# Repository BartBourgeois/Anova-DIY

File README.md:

# Anova Precision Cooker Pro: reverse engineering & firmware recovery

> **Public export.** This repository is a periodic export of a private working repo. Issues and pull
> requests are welcome, but changes are made upstream and arrive with the next sync. The unit's serial
> number and the support ticket number are withheld; see "Legal and safety" below.
> Last sync: 2026-11-26.

Reverse-engineering notes, tools and recovery work for the **Anova Precision Cooker Pro (AN600)**.
The first goal was to **get a unit that died after an interrupted OTA firmware update cooking again**, by fixing
its original main board if that could reasonably be done, otherwise by building our own. **Done on 6 November 2026,
on the original board.** The rest goes on: the hardware mapped further, the schematics, diagnostics software.

**Any%.** My update stopped at 75 %; yours may have frozen on another number, so this project goes by Any%.
Speedrunners know the category: finish, by whatever route works. We got there: nine days from the stalled update to
the first cook.

## It cooks again (6 November 2026)

Dead on 29 October, the morning after an update stalled at 75 %. Cooking again on 6 November, on its original main
board: the buttons and the display, Wi-Fi and the app, and a 54 °C test cook held on point for ten minutes.

- **What was wrong:** the Wi-Fi chip had locked itself. Its security-alert counter stood at the limit, where the
  chip refuses to run until it is reprogrammed. The update's leftovers on the flash were harmless (the chip's own
  safeguard undoes them), the update never reached the Bluetooth chip, and the power board was fine all along.
  What raised the alerts is still open.
- **How it was fixed:** both chips' flash backed up first, each read twice with the same checksum. Then the Wi-Fi
  chip was reprogrammed through its own boot loader with the chip maker's tool: the current firmware, and the unit's
  own files carried over from the backup. Only the chip maker's documented procedures; no firmware is published here.
- **The story:** [Day six: it cooks again](blog/posts/2026-11-06-it-cooks-again.md). The record:
  [timeline](docs/timeline.md). The procedures: the [flash backup handbook](docs/flashbackup/index.md) and the
  [recovery handbook](docs/recovery/index.md).

> Not affiliated with or endorsed by Anova Applied Electronics, Inc. (Anova Culinary). Everything here is at your own risk.
> The power board carries **mains voltage**. Never open or probe a unit that is plugged in.

## Why

*Written on 2 to 4 November, while the cooker was dead, and left as it was written. Its questions are answered in
[It cooks again](#it-cooks-again-6-november-2026).*

I paid what a premium product from a premium brand costs, about $450, and expected exactly that. The cooker died
right after a firmware update was interrupted. Not dropped, not flooded, not abused: the update stalled at 75 %, and
after a power cycle the unit was dead. No beep, no display, nothing. I have no doubt the update killed it: it was the only event, the timing matches, nothing else happened.
By this repo's own standard that stays "likely" until a measurement rules out a coincidental power-supply failure.
The first one, on 4 November, points that way: the power board still puts 5.01 V on the connector with the main board
unplugged. Whether it holds up under load is the next check.

In my view that should not be possible in 2026. A $10 smart plug routinely survives a botched update: it keeps the
old firmware until the new one has proven itself. The Wi-Fi chip in this cooker even has that mechanism built in
(TI documents an OTA rollback for it). Yet here we are.

I'll own my part. The cooker worked perfectly, and I updated it anyway. I work in IT, where update discipline is
drilled into you, and I also know the older rule: if it isn't broken, don't fix it. So yes, I pressed the button.
But in my book, a vendor that offers updates is responsible for what an interrupted one does. The hardware that
lets a device survive a botched update is a second copy of the firmware in flash, a dollar's worth of memory at
most. This cooker has 8 MiB of flash, and its chip's maker documents a rollback mechanism for exactly this case
([recovery-strategy.md](docs/firmware/recovery-strategy.md)). It didn't save my cooker. Finding out why is part of
this project.

And that is the most interesting question in this whole story. The mechanism exists on this very board, so there are
only three ways to end up here: the firmware doesn't use it; or the update touched something it doesn't cover (the
BLE chip, the file system itself); or the failure isn't in the Wi-Fi chip at all. The flash dump will tell. Whichever
answer it is, it goes here, with the evidence.

Anova's answers so far (ticket opened 2026-10-29): leave it plugged in overnight; then that the unit is out of
warranty; then 10 % off a new one. For perspective: 10 % is the usual newsletter sign-up discount on Anova's own
site, and the Pro itself has sold at about half price in seasonal promotions (Amazon US, Black Friday 2020;
[sources](docs/references.md#anova)). On 2026-11-01 I asked for one of four things: a firmware image with recovery
instructions, a replacement main board at my cost, a mail-in reflash, or a refurbished unit. None of the four came:
the reply (2026-11-02) was a reset procedure on the touch panel, which had been dark since the update. On 2026-11-06,
with the cooker cooking again, I told them how it was fixed and offered the details to their firmware team; on
2026-11-08 they forwarded my account to their engineering and development teams. The whole exchange is on record, word for word: [correspondence](docs/correspondence.md). To me, a discount on
a replacement isn't support, it's a sales offer.

It's sad, and I feel tricked: a premium price should buy an update process that can't kill the device. I'd rather
spend thousands of euros on debugging hardware, beta boards and DIY electronics than buy a new Anova. Spent on
tools so far: about €545, two days in ([list](docs/hardware/bench-setup.md#spent-so-far-2026-11-02)).

So I'll keep at this until this dead Pro cooks again, whatever it takes. If Anova helps: good, cheaper for me, and I'll
say so here. If not, make no mistake, the cooker will cook. Everything I learn on the way is in this repo, so the next
person with a dead one doesn't start from zero.

This repository stays online, whatever the outcome. I will not delete it. It documents the progress and the process as
they happen: every change upstream is published within seconds. The public repository is a snapshot by design, the
current state and nothing else; the dated record is the [timeline](docs/timeline.md), and when a statement of
substance about the cooker turns out wrong, the correction goes there with its date. It is what it is.

raptox

## What this project wants

1. **This cooker cooking again.** **Done, 6 November 2026**, on its original main board
   ([how](#it-cooks-again-6-november-2026)). Nothing waited on anyone.
2. **A documented recovery path for every Precision Cooker Pro that fails the same way.** Everything learned here is
   public under an open licence ([LICENSE.md](LICENSE.md)), so the next owner starts from this page, not from zero.
3. **From Anova, any of the four things asked on 2026-11-01:** a firmware image with recovery instructions, a
   replacement main board at my cost, a mail-in reflash, or a refurbished unit. Or, better for every owner: an
   official, documented recovery procedure for units out of warranty. Help gets credited here, in full.

How the work is done: read-only first, a verified backup before any write, every claim with a confidence label and
a source, every step in the [timeline](docs/timeline.md). This project documents a repair. It distributes no firmware
and publishes no way around any protection (see [Legal and safety](#legal-and-safety)).

## The patient

| | |
|---|---|
| Model | Anova Precision Cooker Pro, type **AN600-20** (EU, 220-240 V) |
| FCC ID | [`2APBOAN600`](https://fccid.io/2APBOAN600) (granted 2018-09-16, tested as AN600-10 / 120 V) |
| Symptom | OTA update via the Anova app stalled at 75%. After a power cycle the unit is completely dead: no beep, no display, no LEDs, and nothing on Bluetooth or Wi-Fi. |
| Status | **Cooking again since 2026-11-06**: the Wi-Fi chip had locked itself; reprogrammed ([how](#it-cooks-again-6-november-2026)). |
| Reference | A second, **working** Precision Cooker Pro is available for read-only comparison. |

Full story: [docs/incident.md](docs/incident.md). Everything since then, dated: [docs/timeline.md](docs/timeline.md).
The narrative, in instalments: [blog](blog/index.md).

**Website:** <https://cooked.raptox.be/>, rebuilt from this repo on every push.

## What's inside

From raptox's unit (main board, 2026-11-01) and the FCC photos (everything else).

| Board | Key parts |
|---|---|
| **Main board** `ANOVA_PRO_MAIN_V2.0` | **U1 TI CC3220S** Wi-Fi MCU, boots from **U15/U16 XMC XM25QH64A** (8 MiB SPI NOR, SOP-8 208 mil) · **U7 TI CC2640R2F** BLE MCU (internal flash) · unidentified U14 `T3018` (QFN-40), U13 `4637` (QFN-20, next to the speaker) · debug: J29 (1x3, empty: the serial link between the two chips, both directions, and the Wi-Fi chip's boot-loader port), J14 (4-way DIP footprint, empty, the Wi-Fi chip's three boot straps), Tag-Connect J37/J38, TP groups · 30-pin FPC J8 to the power board · J9 speaker · 6 touch keys, about 135 discrete LEDs forming 3 x 4 seven-segment digits |
| **Power board** `ANOVA_PRO_POWER_REV01` | AC/DC flyback daughterboard (F1 T2A/250V) · heater relay · main fuse · DC/DC buck (6.8 uH) · several unidentified ICs · 30-pin FPC J8 · wire terminals for heater/pump/sensors · PCB "finger" that probably carries the water-temperature sensor |

Details: [docs/hardware/overview.md](docs/hardware/overview.md) ·
[main board](docs/hardware/main-board.md) · [power board](docs/hardware/power-board.md) ·
[component list](docs/hardware/components.md) · [opening the head](docs/hardware/disassembly.md) ·
[bench setup & debugging](docs/hardware/bench-setup.md) · [photo log](docs/photos.md)

## Annotated photos

**raptox's unit**, main board component side, stitched from 335 microscope frames (2026-11-03):

At 100 % (229 px/mm): the zoomable [mosaic viewer](docs/mosaics.md) or the
[lossless PNG](https://github.com/BartBourgeois/Anova-DIY/releases/download/mosaics/2026-11-03_main_component-side_mosaic.png).

The first phone photo of the same side (2026-11-01): [annotated](images/annotated/main_component-side_own.png).

**All photos in this project are our own unless marked otherwise.** The images below marked "FCC" come from the
public FCC filing for this product (FCC ID 2APBOAN600, internal-photos exhibit 3999178, 2018 sample) and carry that
source in their legend.

FCC sample (2018), source: FCC ID 2APBOAN600, exhibit 3999178:

| | |
|---|---|
|  |  |
| Main board, component side | Main board, LED / touch side |
|  |  |
| Power board, top | Power board, bottom |
|  |  |
| Head opened (assembly) | Front bezel (from the back) |

Box colour = category, outline = confidence (solid confirmed, dashed likely, dotted guess).
Click an image for its callout table.

## Roadmap

Two cases, both planned, in [docs/roadmap.md](docs/roadmap.md): Anova helps (unlikely; documented in full if it
happens, and the repair part ends there), or we do it ourselves, all the way, with every step the tools allow. Either
way the project doesn't stop at the point of no return, which has passed.

The headline steps of the do-it-ourselves case: **4K microscope imaging of every board**, tile by tile, into
measurable mosaics; transillumination for the inner copper layers; **reverse-engineering the schematics**, net by net,
since Anova's are confidential in the FCC filing; logic analyser and UART on the boot sequence; a verified dump of the
flash; rehearsals of every write on a known-good chip; and, if the board can't be fixed, a board of our own. The
phase view below is the short version.

| Phase | Goal | Status |
|---|---|---|
| 0 | Document hardware from the public FCC filing | **done (first pass)** |
| 1 | Open the dead unit: own high-res photos, read chip markings, measure supply rails; compare (read-only) with the working unit | **in progress**: opened, main board photographed, markings read; main board's component side stitched from microscope frames at about 229 px/mm ([photo log](docs/photos.md#2026-11-03-microscope-mosaic-main-board-component-side)); next: the other sides and backlight; the power board's 5 V measured (4 Nov), the rails under power todo |
| 2 | Find and map debug interfaces: J29, J37/J38 (Tag-Connect), DIP J14, test points; CC3220 SOP straps, UART, JTAG/SWD; CC2640R2F cJTAG. Identify power-board U2 (MCU?) and map the J8 pinout unpowered. Draw the schematics from the images and the continuity map. | **in progress**: J8's supply and ground (4 Nov); the flash bus, the three boot straps with their pull-downs, the serial header J29 and nine bare pads measured to the chips (5 Nov, [test points](docs/hardware/testpoints.md)); J37 and J8's signal lines next |
| 3 | **Back up first**: full read-only dump of the CC3220 serial flash (and of the CC2640R2F flash if readable), read twice and hash-verified | **done**, 6 Nov: the serial flash by clip with the Wi-Fi chip held in reset, the CC2640R2F over its cJTAG port; each read twice, identical, copied off the machine ([flash backup handbook](docs/flashbackup/index.md)) |
| 4 | Analyse the dumps: SimpleLink filesystem layout, OTA state, which chip the failed update targeted | **done**, 6 Nov: the file system intact, the interrupted update in a state the chip rolls back; the CC2640R2F untouched by it; the CC3220 **locked** (its security-alert counter at the limit) ([timeline](docs/timeline.md)) |
| 5 | Recovery, depending on Phase 4. The broken file alone, replaced through the UARTLOAD boot loader, keeps the unit's network address and cloud identity, but a production-mode boot loader refuses file writes (rehearsed 6 Nov); then a full image with the unit's own readable files carried over from the backup, or RET_FACTORY_IMAGE (both erase the protected ones); a CC2640R2F reflash if that chip is the victim | **done**, 6 Nov: a full image through the UARTLOAD boot loader, the current firmware with the unit's own files from the backup; the lock cleared, **the cooker cooks** ([the story](blog/posts/2026-11-06-it-cooks-again.md)) |
| 6 | Diagnostics software (UART console, flash-dump parser, BLE/Wi-Fi local API client, ...) | later |
| B | If the board can't reasonably be fixed: our own main board (ESP32-S3, headless first), or our own firmware on the original CC3220 | **committed fallback** ([plan B](docs/plan-b-custom-mainboard.md)) |

The recovery reasoning lives in [docs/firmware/recovery-strategy.md](docs/firmware/recovery-strategy.md).

Phases 1-2 are run as an **open exploration**: no gates, every tool used to learn as much as it can, route chosen
only when the findings make it obvious.

## Legal and safety

- **Not affiliated.** Anova and Precision Cooker are trademarks of Anova Applied Electronics, Inc., used here only
  to identify the product. This project is not affiliated with, endorsed by or sponsored by Anova.
- **Own device, for repair.** Everything here comes from examining a device raptox owns, from public FCC filings and
  from public chip-maker documentation (TI). The aim is to repair it. The procedures described are the ones TI
  documents for its own chips; in the author's reading (not legal advice), nothing here circumvents a technical
  protection.
- **Never distributed:** Anova firmware, flash dumps or fragments of them; keys, certificates or credentials; anything
  that gives access to Anova's servers; Anova's user manual; the FCC exhibit PDFs themselves (public at
  [fccid.io/2APBOAN600](https://fccid.io/2APBOAN600), SHA-256 in [docs/references.md](docs/references.md)).
- **Statements about Anova** are dated facts from the support correspondence, quoted word for word on the
  [correspondence page](docs/correspondence.md) or paraphrased, or opinions labelled as such. Anova staff are never named.
- **Safety, no warranty.** The power board carries mains voltage, which can kill. Opening the unit voids its warranty
  and its CE/FCC certification, radio included; a modified unit is not a certified appliance. Never leave a modified
  heater unattended. Everything here is at your own risk, without warranty or liability of any kind
  ([LICENSE.md](LICENSE.md), at the root of the public repo).
- The author is an engineer, not a lawyer. This is engineering documentation, not legal advice.
- The full statement of the bounds this project works within, for the United States, for Belgium and the EU, and for
  everywhere else: [docs/legal.md](docs/legal.md).

## Sources

Hardware information comes from raptox's own unit and the public FCC filing for `2APBOAN600` (the schematics and block
diagram are confidential and not available). See [docs/references.md](docs/references.md).

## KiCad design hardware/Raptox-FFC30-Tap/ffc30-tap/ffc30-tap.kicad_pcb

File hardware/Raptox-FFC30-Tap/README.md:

# FFC30 tap

A gated pass-through board for any 30-way flat flex cable (FFC) at 0.5 mm pitch. It sits between two boards, brings
every line out on a 2.54 mm **bus** pin with a ground pin beside it (for a logic analyser such as the DSLogic Plus),
and puts a **jumper gate** on each side: a cap per line decides whether that line of side A, of side B, or of both
reaches the bus. Every cap on = a plain pass-through. Nothing on the board is specific to one device; it was first
made for the Anova Precision Cooker Pro's J8 link ([pinout](../../docs/hardware/j8.md)).

**Status (2026-11-18): rev D drawn, not ordered** (in [ffc30-tap/](ffc30-tap/), DRC clean). **Rev C is in production
at JLCPCB** (ordered 2026-11-12, 5 boards, fully assembled), frozen with its own instructions in [revC/](revC/README.md).

## Rev D
- 96 x 92 mm, 4 layers, 1.6 mm, black solder mask.
- Two sockets, the same part on both sides: HanElectricity **05A20L30P** (LCSC C5362159), bottom contact, flip lock,
  2.0 mm high, for 0.3 mm FFC. Contacts on one face only, so neither cable can go in upside down. Land pattern from
  HanElectricity's drawing 05A20LXX (rev A, 2015-05-03): signal pads 0.30 x 1.25 mm, mounting pads 2.00 x 3.00 mm.
  The body's front (cable entry) is flush with the board edge (`likely`, within about 0.2 mm). Unchanged from rev C.
- **One row per line, 30 rows** (pin 30 at the top, pin 1 at the bottom, in the order of the socket pads), six pins
  a row in three pairs, one empty pitch between the pairs so a cap can't bridge two of them:

  ```
  socket A ─ [ A   BUS ]   [ BUS  GND ]   [ BUS   B ] ─ socket B
               gate A          bus           gate B
  ```
  - **A n** = the left socket's pin n, **B n** = the right socket's pin n, **BUS n** = the three BUS pins of row n
    (one net).
  - Cap on **A|BUS**: side A's line n on the bus. Cap on **BUS|B**: side B's line n on the bus. Both: line n passes
    through, as in rev C. Neither: the two sides are apart on that line, and each can be probed or driven on its own.
  - Cap on **BUS|GND**: line n joined to the ground rail, as in rev C. The rail (the GND column and the two inner
    ground planes) floats until one is on.
- Six 2x15 headers (LCSC C56496, 2.54 mm, straight), two per pair, butted end to end at the middle (pins 15 and 16).
- Every line on the top layer: a 45 degree fan-out from each socket straight into its outer column; the BUS link from
  the bus pair to gate B runs round the ground pin in the gap below its row. In1 and In2 are solid ground planes.
- Silkscreen: the row numbers (in both gaps), the column and pair names, SIDE A / SIDE B, the ground box, the title
  and cooked.raptox.be.

## Using it
1. **Cables:** both of the same type (contacts on the same side at both ends, "type A"), contacts down into the
   sockets.
2. **The board whose pin numbers you want goes in the LEFT socket (side A).** Row n is then its pin n, if its
   connector has bottom contacts and numbers its pins like these sockets (pin 1 on the left, seen from where the
   cable enters). Otherwise row n is its pin 31 - n. The lines pass through correctly either way.
3. **Before power,** with the caps on and only one board's cable in, ring the pins you know (its supply pins
   together, its ground pins together) to make sure of the numbering.
4. **Gates, in this order:** ground lines first (A|BUS and BUS|B on every ground row), then the supply, then the
   signals; take them off in the reverse order. A side with its supply connected and its ground open finds a ground
   through the signal lines and the chips' protection diodes.
5. **Ground rail:** a cap on BUS|GND only on a row that *is* ground. A cap there on a supply row shorts the supply.
   One or two are enough for slow signals (DreamSourceLab's DSView guide: one common ground below about 5 MHz).
6. **Probes:** the signal lead on a BUS pin (or on an A or B pin to see one side before its gate), its ground lead on
   the GND pin of the row.
7. **Mains:** a PC-grounded analyser connects the PC's earth to the board's ground. With a mains-powered board in the
   chain, check that its ground is isolated from mains first.
8. **Underneath:** the header pins stick out about 1.4 mm under the board (3 mm tails through 1.6 mm), plus solder.
   Stand the board on four M2 nylon standoffs, at least 6 mm, in the corner holes, or on a non-conductive surface.
   Never on metal: it joins pins, and a supply line on ground shorts the supply.

## Ordering at JLCPCB
Three files, all in `ffc30-tap/fab/`:

| Step | File | Settings |
|---|---|---|
| PCB | `ffc30-tap_gerbers_JLC.zip` | 4 layers, 96 x 92 mm (read from the files), 1.6 mm, **black** solder mask, the default 4-layer stackup |
| Assembly | | **Standard** PCBA (the headers are wave soldered, which Economic doesn't do), top side, edge rails as JLCPCB asks (rev C had them on the sides without sockets), **Confirm Parts Placement: Yes** |
| BOM | `jlc_bom.csv` | J1, J2 = C5362159 (socket); J3-J8 = C56496 (2x15 header). Both are extended parts; check stock |
| Placement | `jlc_cpl.csv` | Check every part in the placement preview, then confirm |

The CPL already carries two corrections for JLCPCB's own part models (measured in their placement viewer on
2026-11-12, set in `build_fab.py`; the copper itself follows the makers' drawings):
- **Sockets J1, J2:** JLCPCB's model of C5362159 sat 2.0 mm toward the board edge from the pads, so the CPL moves each
  socket 2.0 mm toward its pads. With that, the model's pins end about 0.15 mm inside the pads' tips and its body
  starts about 0.8 mm from them, as the footprint assumes.
- **Headers J3-J8:** JLCPCB's model of C56496 lies across the board at 0 degrees; the CPL turns them 90 degrees.

Still check in the placement preview, against [the render](ffc30-tap/render_top.png): the sockets' cable openings
face the board edges and their pins sit on the 30 pads; the headers stand over their two columns, two butted end to end per pair.

Rev C's first quote (2026-11-12, 5 boards, before shipping): PCB EUR 14.40 (black mask EUR 7.20 of it), Standard PCBA
EUR 43.39, total EUR 57.79; PCB 3 days, assembly 5-6 days.

## Regenerating
The board is generated from code: change `generate_board.py`, never the `.kicad_pcb` by hand. With KiCad 10's own
Python, in `ffc30-tap/`:

```sh
"<KiCad 10>/bin/python.exe" -I generate_board.py   # board, footprint library, fp-lib-table
"<KiCad 10>/bin/python.exe" -I build_fab.py        # DRC (must be clean), gerbers, drill, BOM, CPL, renders
```

## Revisions
- **rev A** (2026-11-12, [revA/](revA/), not ordered): 2 layers, one 2x15 header, sockets with contacts on both faces
  (X05A20H30G). One cable inserted upside down mirrors the bus (pin n to 31 - n): on the cooker that feeds the main
  board backwards. Its header numbers read reversed with the main board in the socket marked HOST.
- **rev B** (drawn, not kept): four columns of 15 (ground, line, line, ground) with ground planes.
- **rev C** (2026-11-12, [revC/](revC/), **ordered**, in production since 2026-11-18): frozen as sent to JLCPCB
  (`fab/ffc30-tap_gerbers_JLC.zip` SHA-256 `b90ba95b…403c0a`, `jlc_bom.csv` `8b6289e8…3837`, `jlc_cpl.csv`
  `60cd19c0…7c69`); never regenerate it. Its first build still carried rev A's socket pads; the X05A20LXXT land pattern
  replaced them the same day, before any order (the board grew to 80 x 70 mm). The same day the socket became
  HanElectricity's 05A20L30P (XKB's was out of stock at JLCPCB), with its own land pattern.
- **rev D** (2026-11-18, [ffc30-tap/](ffc30-tap/), not ordered): a jumper gate on each side of rev C's bus, one row
  per line (A, BUS | BUS, GND | BUS, B), every line gated, grounds included. 96 x 92 mm, six 2x15 headers, every
  line on the top layer. Universal: no device-specific notes on the board or in its instructions.

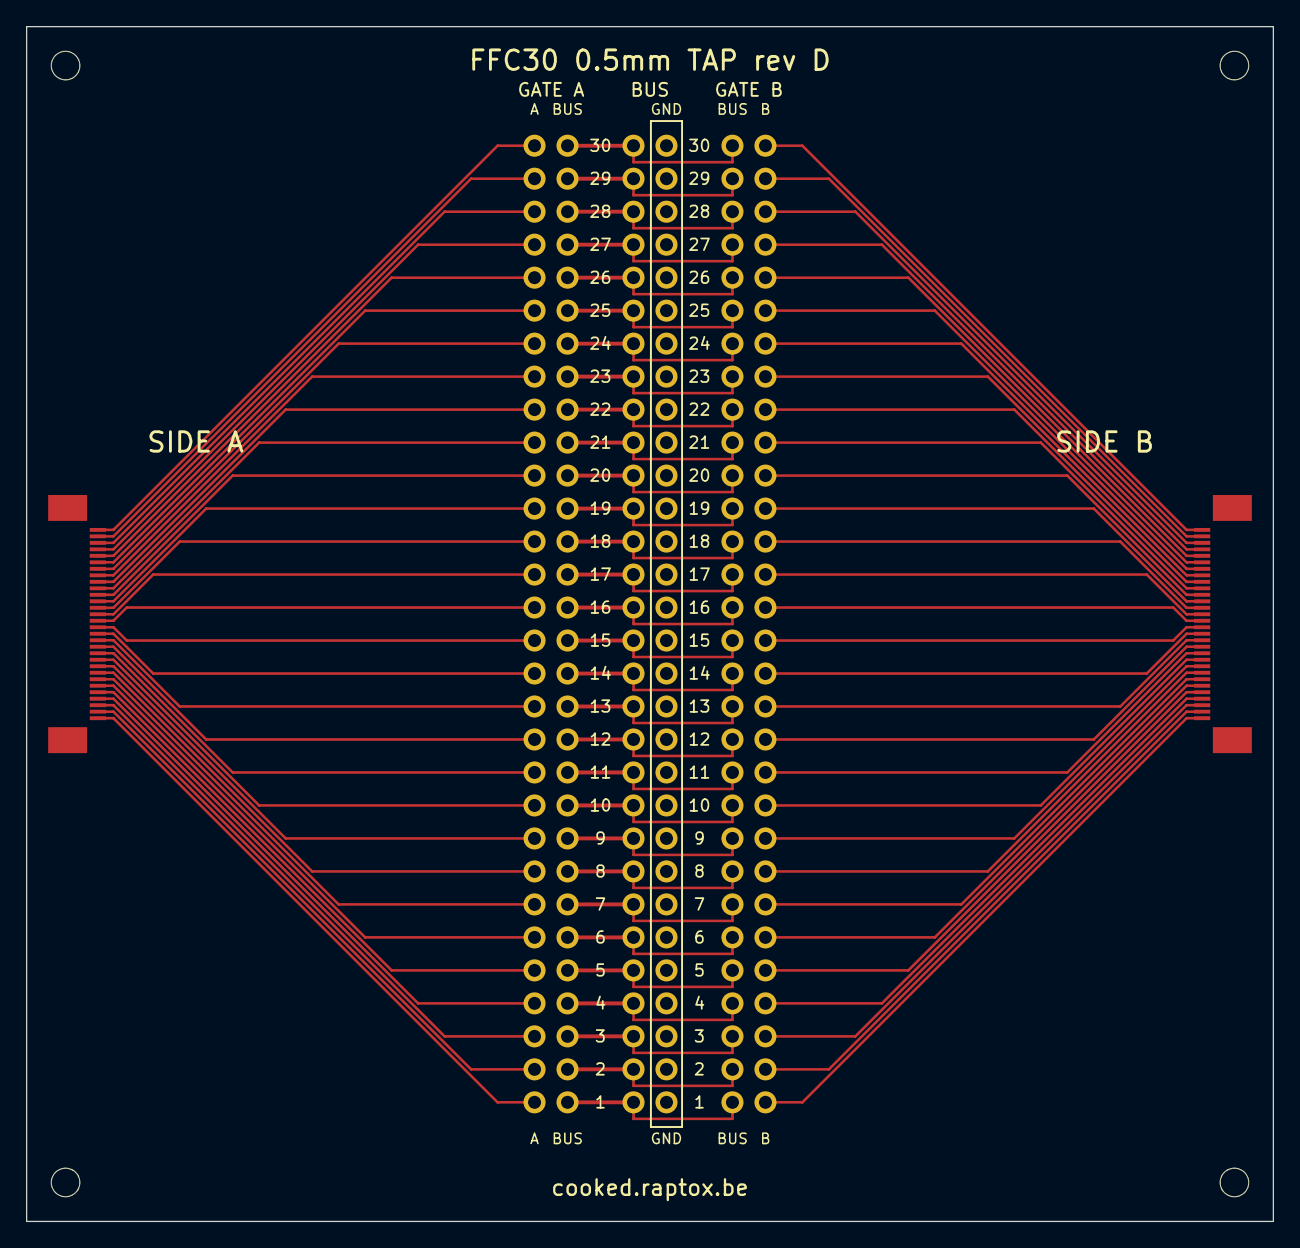
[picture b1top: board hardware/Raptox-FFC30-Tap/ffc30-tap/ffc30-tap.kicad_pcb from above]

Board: 4 copper layers, 96.0 x 92.0 mm, 12 parts (0 on the bottom side), 91 nets.

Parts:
H1, H2, H3, H4: M2; MountingHole_2.2mm_M2
J1, J2: HanElectricity 05A20L30P; HanElectricity_05A20L30P_FPC30_P0.5mm
J3, J4, J5, J6, J7, J8: BOOMELE 2.54-2*15P (2x15 2.54 mm male, straight); PinHeader_2x15_P2.54mm_Vertical_centred

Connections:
A01: J1.30, J4.29
A02: J1.29, J4.27
A03: J1.28, J4.25
A04: J1.27, J4.23
A05: J1.26, J4.21
A06: J1.25, J4.19
A07: J1.24, J4.17
A08: J1.23, J4.15
A09: J1.22, J4.13
A10: J1.21, J4.11
A11: J1.20, J4.9
A12: J1.19, J4.7
A13: J1.18, J4.5
A14: J1.17, J4.3
A15: J1.16, J4.1
A16: J1.15, J3.29
A17: J1.14, J3.27
A18: J1.13, J3.25
A19: J1.12, J3.23
A20: J1.11, J3.21
A21: J1.10, J3.19
A22: J1.9, J3.17
A23: J1.8, J3.15
A24: J1.7, J3.13
A25: J1.6, J3.11
A26: J1.5, J3.9
A27: J1.4, J3.7
A28: J1.3, J3.5
A29: J1.2, J3.3
A30: J1.1, J3.1
B01: J2.1, J8.30
B02: J2.2, J8.28
B03: J2.3, J8.26
B04: J2.4, J8.24
B05: J2.5, J8.22
B06: J2.6, J8.20
B07: J2.7, J8.18
B08: J2.8, J8.16
B09: J2.9, J8.14
B10: J2.10, J8.12
B11: J2.11, J8.10
B12: J2.12, J8.8
B13: J2.13, J8.6
B14: J2.14, J8.4
B15: J2.15, J8.2
B16: J2.16, J7.30
B17: J2.17, J7.28
B18: J2.18, J7.26
B19: J2.19, J7.24
B20: J2.20, J7.22
B21: J2.21, J7.20
B22: J2.22, J7.18
B23: J2.23, J7.16
B24: J2.24, J7.14
B25: J2.25, J7.12
B26: J2.26, J7.10
B27: J2.27, J7.8
B28: J2.28, J7.6
B29: J2.29, J7.4
B30: J2.30, J7.2
BUS01: J4.30, J6.29, J8.29
BUS02: J4.28, J6.27, J8.27
BUS03: J4.26, J6.25, J8.25
BUS04: J4.24, J6.23, J8.23
BUS05: J4.22, J6.21, J8.21
BUS06: J4.20, J6.19, J8.19
BUS07: J4.18, J6.17, J8.17
BUS08: J4.16, J6.15, J8.15
BUS09: J4.14, J6.13, J8.13
BUS10: J4.12, J6.11, J8.11
BUS11: J4.10, J6.9, J8.9
BUS12: J4.8, J6.7, J8.7
BUS13: J4.6, J6.5, J8.5
BUS14: J4.4, J6.3, J8.3
BUS15: J4.2, J6.1, J8.1
BUS16: J3.30, J5.29, J7.29
BUS17: J3.28, J5.27, J7.27
BUS18: J3.26, J5.25, J7.25
BUS19: J3.24, J5.23, J7.23
BUS20: J3.22, J5.21, J7.21
BUS21: J3.20, J5.19, J7.19
BUS22: J3.18, J5.17, J7.17
BUS23: J3.16, J5.15, J7.15
BUS24: J3.14, J5.13, J7.13
BUS25: J3.12, J5.11, J7.11
BUS26: J3.10, J5.9, J7.9
BUS27: J3.8, J5.7, J7.7
BUS28: J3.6, J5.5, J7.5
BUS29: J3.4, J5.3, J7.3
BUS30: J3.2, J5.1, J7.1
GND: J5.2, J5.4, J5.6, J5.8, J5.10, J5.12, J5.14, J5.16, J5.18, J5.20, J5.22, J5.24, J5.26, J5.28, J5.30, J6.2, J6.4, J6.6, J6.8, J6.10, J6.12, J6.14, J6.16, J6.18, J6.20, J6.22, J6.24, J6.26, J6.28, J6.30

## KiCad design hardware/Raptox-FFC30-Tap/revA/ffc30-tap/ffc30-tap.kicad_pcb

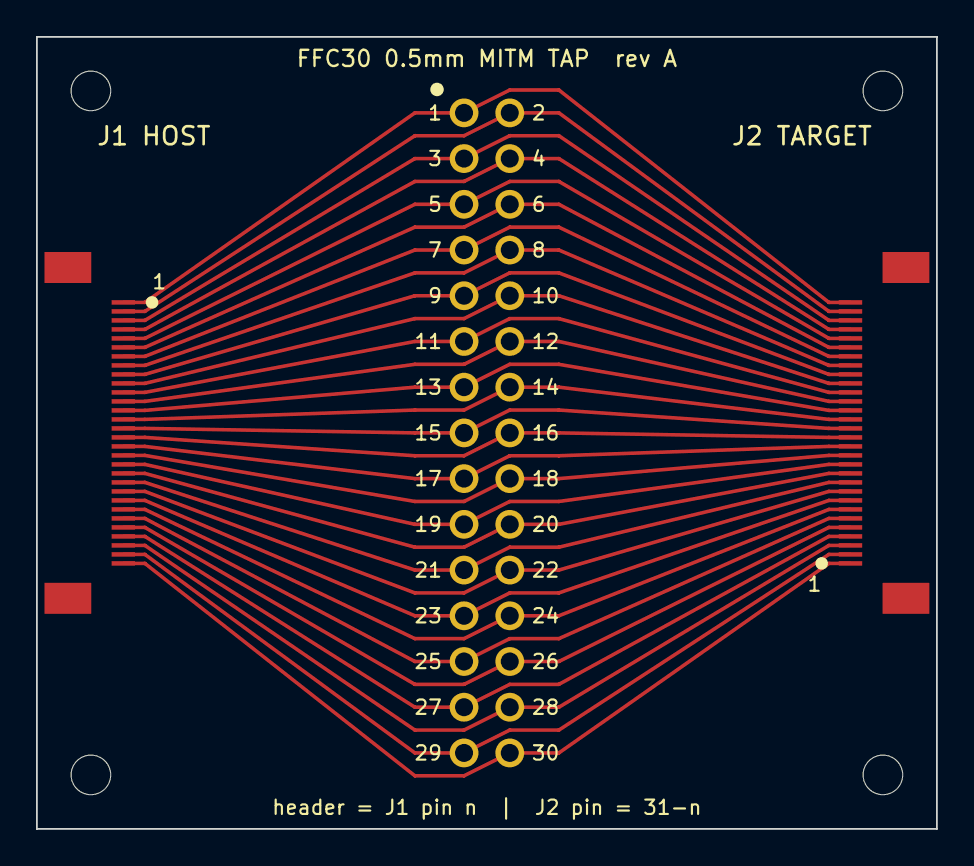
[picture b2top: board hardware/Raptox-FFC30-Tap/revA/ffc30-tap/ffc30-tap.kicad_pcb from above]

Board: 2 copper layers, 50.0 x 44.0 mm, 7 parts (0 on the bottom side), 30 nets.

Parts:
H1, H2, H3, H4: M2
J1: FPC30 host side; XKB_X05A20H30G_FPC30_P0.5mm
J2: FPC30 target side; XKB_X05A20H30G_FPC30_P0.5mm
J3: Tap 2x15 2.54mm; PinHeader_2x15_P2.54mm_tap

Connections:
S01: J1.1, J2.30, J3.1
S02: J1.2, J2.29, J3.2
S03: J1.3, J2.28, J3.3
S04: J1.4, J2.27, J3.4
S05: J1.5, J2.26, J3.5
S06: J1.6, J2.25, J3.6
S07: J1.7, J2.24, J3.7
S08: J1.8, J2.23, J3.8
S09: J1.9, J2.22, J3.9
S10: J1.10, J2.21, J3.10
S11: J1.11, J2.20, J3.11
S12: J1.12, J2.19, J3.12
S13: J1.13, J2.18, J3.13
S14: J1.14, J2.17, J3.14
S15: J1.15, J2.16, J3.15
S16: J1.16, J2.15, J3.16
S17: J1.17, J2.14, J3.17
S18: J1.18, J2.13, J3.18
S19: J1.19, J2.12, J3.19
S20: J1.20, J2.11, J3.20
S21: J1.21, J2.10, J3.21
S22: J1.22, J2.9, J3.22
S23: J1.23, J2.8, J3.23
S24: J1.24, J2.7, J3.24
S25: J1.25, J2.6, J3.25
S26: J1.26, J2.5, J3.26
S27: J1.27, J2.4, J3.27
S28: J1.28, J2.3, J3.28
S29: J1.29, J2.2, J3.29
S30: J1.30, J2.1, J3.30
